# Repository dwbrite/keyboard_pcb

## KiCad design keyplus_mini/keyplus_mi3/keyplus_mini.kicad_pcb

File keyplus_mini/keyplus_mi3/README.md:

# keyplus mini v3 (imperial)

## Firmware

[See here](https://github.com/ahtn/keyplus)

## License

[CC-BY-SA](https://creativecommons.org/licenses/by-sa/4.0/)

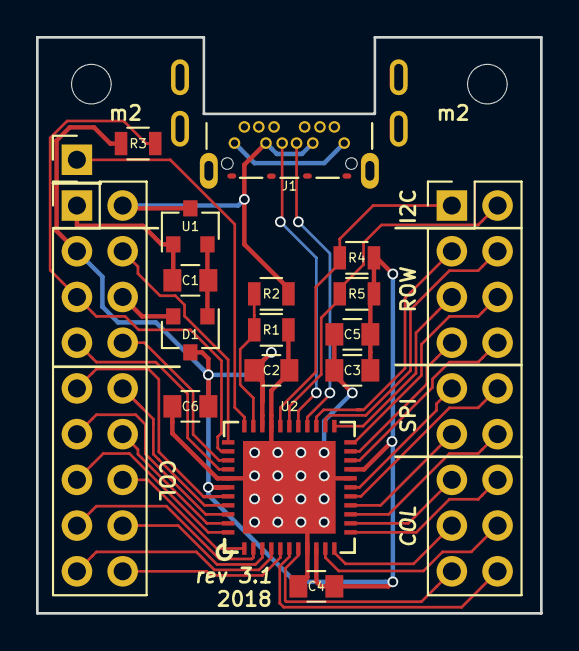
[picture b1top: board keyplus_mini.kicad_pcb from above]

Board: 2 copper layers, 28.0 x 32.0 mm, 18 parts (0 on the bottom side), 41 nets.

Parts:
C1: 1uF; C_0805
C2: 10uF; C_0805
C3, C4, C5, C6: 0.1uF; C_0805
D1: D_Schottky_x2_KCom_AAK; SOT-23
J1: USB_C_Receptacle; CUI_USB_C_Padless
J2, J4: Conn_02x09_Odd_Even; Pin_Header_Straight_2x09_Pitch2.54mm
J3: CONN_01X01; Pin_Header_Straight_1x01_Pitch2.54mm
R1, R2: 100k; R_0805
R3, R4, R5: 10k; R_0805
U1: MCP1700-3302E_SOT23; SOT-23
U2: ATXMEGA-A4U-EPAD; QFN-44-1EP_7x7mm_Pitch0.5mm_Alt_Silk

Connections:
+3V3: C2.2, C3.2, C4.2, C5.2, C6.2, D1.3, J2.3, R3.1, R4.1, R5.1, U2.9, U2.19, U2.31, U2.39
+5V: J1.B4, J1.B9, J2.2, R1.1, U1.3
+BATT: D1.2, J2.6
/D+: J1.B6, U2.27
/D-: J1.B7, U2.26
/PA0: J2.9, U2.40
/PA1: J2.10, U2.41
/PA2: J2.11, U2.42
/PA3: J2.12, U2.43
/PA4: J2.13, U2.44
/PA5: J2.14, U2.1
/PA6: J2.15, U2.2
/PA7: J2.16, U2.3
/PB0: J2.17, U2.4
/PB1: J2.18, U2.5
/PB2: J4.18, U2.6
/PB3: J4.17, U2.7
/PC0: J4.16, U2.10
/PC1: J4.15, U2.11
/PC2: J4.14, U2.12
/PC3: J4.13, U2.13
/PC4: J4.12, U2.14
/PC5: J4.11, U2.15
/PC6: J4.10, U2.16
/PC7: J4.9, U2.17
/PCL: J2.5, R3.2, U2.35
/PD0: J4.8, U2.20
/PD1: J4.7, U2.21
/PD2: J4.6, U2.22
/PD3: J4.5, U2.23
/PD4: J4.4, U2.24
/PD5: J4.3, U2.25
/PDI: J2.4, U2.34
/PE0: J4.2, R5.2, U2.28
/PE1: J4.1, R4.2, U2.29
/PE3: J3.1, U2.33
/PR0: J2.8, U2.36
/PR1: J2.7, U2.37
GND: C1.1, C2.1, C3.1, C4.1, C5.1, C6.1, J1.B1, J1.B12, J2.1, R2.2, U1.1, U2.8, U2.18, U2.30, U2.38, U2.45
unnamed: C1.2, D1.1, U1.2
unnamed: R1.2, R2.1, U2.32

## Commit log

2018-07-01 Remove unnecessary directories
2018-07-03 Add new Americanized PCB (mi3)

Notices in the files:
keyplus_mini/keyplus_mi3/keyplus_mini.kicad_pcb:
©dwbrite
©jem
